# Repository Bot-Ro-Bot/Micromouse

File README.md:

# Micromouse
This project was done for participating in International Micromouse Competition organized by
[TechFest2019-20 at IIT Bombay](https://techfest.org/). It is
the furtherance of the Tremaux algorithm by employing a potential value algorithm in conjunction, with improving search in a micromouse.  The fused algorithm running on the STM32 Bluepill microcontroller explores and finds the shortest path in a 16x16 maze. Proximity sensors, gyroscope, and magnetometer together with encoder motors aid the micromouse to understand its surrounding hindrances and make precise movements while traversing through a maze. The optimized algorithm eliminates any paths that may lead the micromouse further away from the center of the maze during the initial run itself and saves a significant amount of time while solving a maze.

## Flow Chart of the Optimized Algorithm

Here are the three different versions of micromouse designed and fabricated. The bot at the center was used during the IMC-2020.

## Citation:
You can find our publication [here](https://ictaes.org/wp-content/uploads/2020/09/IJAE-2020-Vol.03-No.02/7_Sanjaya_Vol3_No2.pdf?ckattempt=1).
```
@article{rijalinternational,
  title={Optimizing Tremaux Algorithm in Micromouse Using Potential Values},
  journal={International Journal of Advanced Engineering},
  author={Rijal, Sanjay and Nepal, Rabin and Lwagun, Rhimesh and Pati, Rohit and Bhatta, Janardan},
  volume={3},
  issue={2},
  year={2020}
}

```

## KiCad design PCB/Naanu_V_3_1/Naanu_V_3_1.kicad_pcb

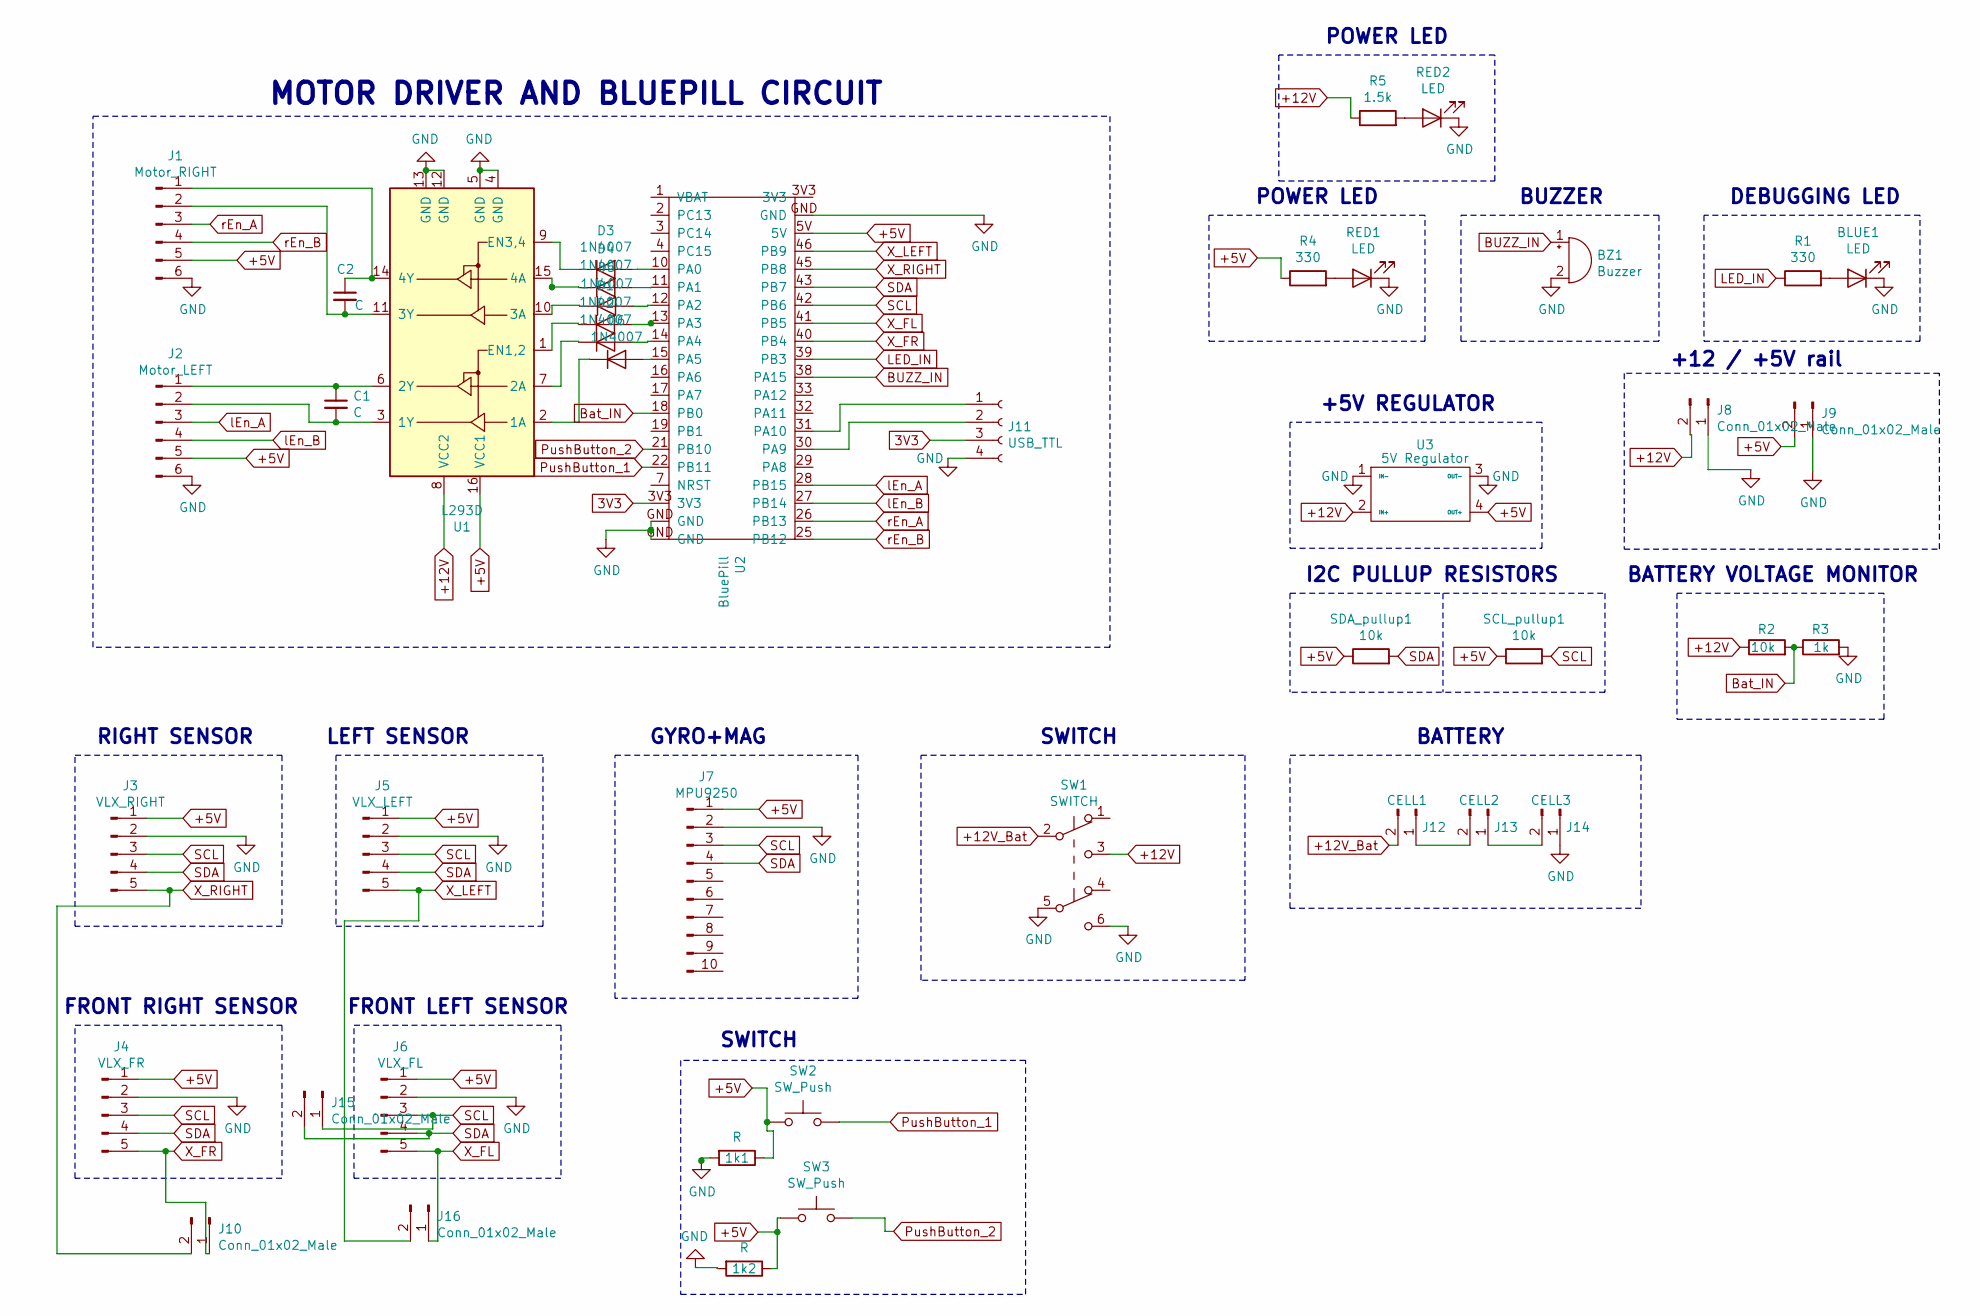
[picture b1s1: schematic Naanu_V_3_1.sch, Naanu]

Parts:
1k1, 1k2: R; R_Axial_DIN0207_L6.3mm_D2.5mm_P7.62mm_Horizontal
BLUE1: LED; LED_D3.0mm
BZ1: Buzzer; Buzzer_15x7.5RM7.6
C1, C2: C; C_Disc_D3.0mm_W1.6mm_P2.50mm
D1, D2, D3, D4, D5, D6: 1N4007; D_DO-41_SOD81_P7.62mm_Horizontal
J1: Motor_RIGHT; PinHeader_1x06_P2.54mm_Vertical
J2: Motor_LEFT; PinHeader_1x06_P2.54mm_Vertical
J3: VLX_RIGHT; PinHeader_1x05_P2.54mm_Horizontal
J4: VLX_FR; PinHeader_1x05_P2.54mm_Horizontal
J5: VLX_LEFT; PinHeader_1x05_P2.54mm_Horizontal
J6: VLX_FL; PinHeader_1x05_P2.54mm_Horizontal
J7: MPU9250; PinHeader_1x10_P2.54mm_Vertical
J8, J9, J10, J15, J16: Conn_01x02_Male; PinHeader_1x02_P2.54mm_Vertical
J11: USB_TTL; PinHeader_1x04_P2.54mm_Vertical
J12: CELL1; PinHeader_1x02_P2.54mm_Horizontal
J13: CELL2; PinHeader_1x02_P2.54mm_Horizontal
J14: CELL3; PinHeader_1x02_P2.54mm_Horizontal
R1, R4: 330; R_Axial_DIN0207_L6.3mm_D2.5mm_P7.62mm_Horizontal
R2: 10k; R_Axial_DIN0207_L6.3mm_D2.5mm_P7.62mm_Horizontal
R3: 1k; R_Axial_DIN0207_L6.3mm_D2.5mm_P7.62mm_Horizontal
R5: 1.5k; R_Axial_DIN0207_L6.3mm_D2.5mm_P7.62mm_Horizontal
RED1, RED2: LED; LED_D3.0mm
SCL_pullup1: 10k; R_Axial_DIN0207_L6.3mm_D2.5mm_P7.62mm_Horizontal
SDA_pullup1: 10k; R_Axial_DIN0207_L6.3mm_D2.5mm_P7.62mm_Horizontal
SW1: SWITCH; SW_CuK_JS202011CQN_DPDT_Straight
SW2, SW3: SW_Push; SW_PUSH_6mm_H5mm
U1: L293D; DIP-16_W7.62mm
U2: BluePill; STM32
U3: 5V Regulator; Buck

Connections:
3V3: J11.3, U2.3V3
+5V: 1k1.1, 1k2.1, J1.5, J2.5, J3.1, J4.1, J5.1, J6.1, J7.1, J9.2, R4.1, SCL_pullup1.1, SDA_pullup1.1, SW2.1, SW3.1, U1.16 (VCC1), U2.5V, U3.4 (OUT+)
+12V: J8.2, R2.1, R5.1, SW1.3 (C), U1.8 (VCC2), U3.2 (IN+)
+12V_Bat: J12.2, SW1.2 (B)
BUZZ_IN: BZ1.1 (-), U2.38 (PA15)
Bat_IN: R2.2, R3.1, U2.18 (PB0)
GND: 1k1.2, 1k2.2, BLUE1.1 (K), BZ1.2 (+), J1.6, J2.6, J3.2, J4.2, J5.2, J6.2, J7.2, J8.1, J9.1, J11.4, J14.1, R3.2, RED1.1 (K), RED2.1 (K), SW1.5 (B), SW1.6 (C), U1.4 (GND), U1.5 (GND), U1.12 (GND), U1.13 (GND), U2.GND, U3.1 (IN-), U3.3 (OUT-)
LED_IN: R1.1, U2.39 (PB3)
unnamed: BLUE1.2 (A), R1.2
unnamed: C1.1, J2.1, U1.6 (2Y)
unnamed: C1.2, J2.2, U1.3 (1Y)
unnamed: C2.1, J1.1, U1.14 (4Y)
unnamed: C2.2, J1.2, U1.11 (3Y)
unnamed: D1.1 (K), U1.1 (EN1,2)
unnamed: D1.2 (A), U2.13 (PA3)
unnamed: D2.1 (K), U1.7 (2A)
unnamed: D2.2 (A), U2.14 (PA4)
unnamed: D3.1 (K), U1.9 (EN3,4)
unnamed: D3.2 (A), U2.10 (PA0)
unnamed: D4.1 (K), U1.15 (4A)
unnamed: D4.2 (A), U2.11 (PA1)
unnamed: D5.1 (K), U1.10 (3A)
unnamed: D5.2 (A), U2.12 (PA2)
unnamed: D6.1 (K), U1.2 (1A)
unnamed: D6.2 (A), U2.15 (PA5)
unnamed: J11.1, U2.31 (PA10)
unnamed: J11.2, U2.30 (PA9)
unnamed: J12.1, J13.2
unnamed: J13.1, J14.2
unnamed: R4.2, RED1.2 (A)
unnamed: R5.2, RED2.2 (A)
PushButton_1: SW2.2, U2.22 (PB11)
PushButton_2: SW3.2, U2.21 (PB10)
SCL: J3.3, J4.3, J5.3, J6.3, J7.3, J15.1, SCL_pullup1.2, U2.42 (PB6)
SDA: J3.4, J4.4, J5.4, J6.4, J7.4, J15.2, SDA_pullup1.2, U2.43 (PB7)
X_FL: J6.5, J16.1, U2.41 (PB5)
X_FR: J4.5, J10.1, U2.40 (PB4)
X_LEFT: J5.5, J16.2, U2.46 (PB9)
X_RIGHT: J3.5, J10.2, U2.45 (PB8)
lEn_A: J2.3, U2.28 (PB15)
lEn_B: J2.4, U2.27 (PB14)
rEn_A: J1.3, U2.26 (PB13)
rEn_B: J1.4, U2.25 (PB12)

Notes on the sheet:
RIGHT SENSOR
LEFT SENSOR
FRONT RIGHT SENSOR
FRONT LEFT SENSOR
GYRO+MAG
SWITCH
I2C PULLUP RESISTORS
BUZZER
DEBUGGING LED
BATTERY VOLTAGE MONITOR
+5V REGULATOR
MOTOR DRIVER AND BLUEPILL CIRCUIT
POWER LED
BATTERY
+12 / +5V rail

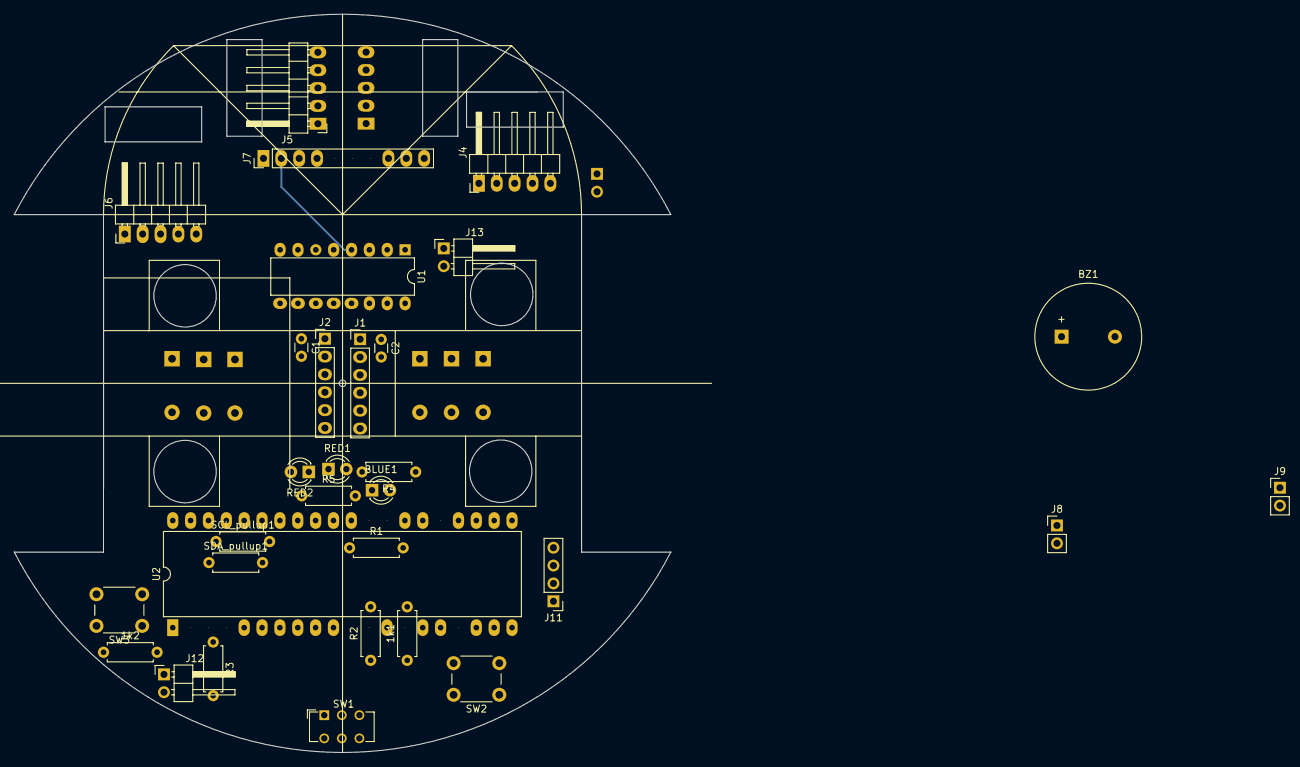
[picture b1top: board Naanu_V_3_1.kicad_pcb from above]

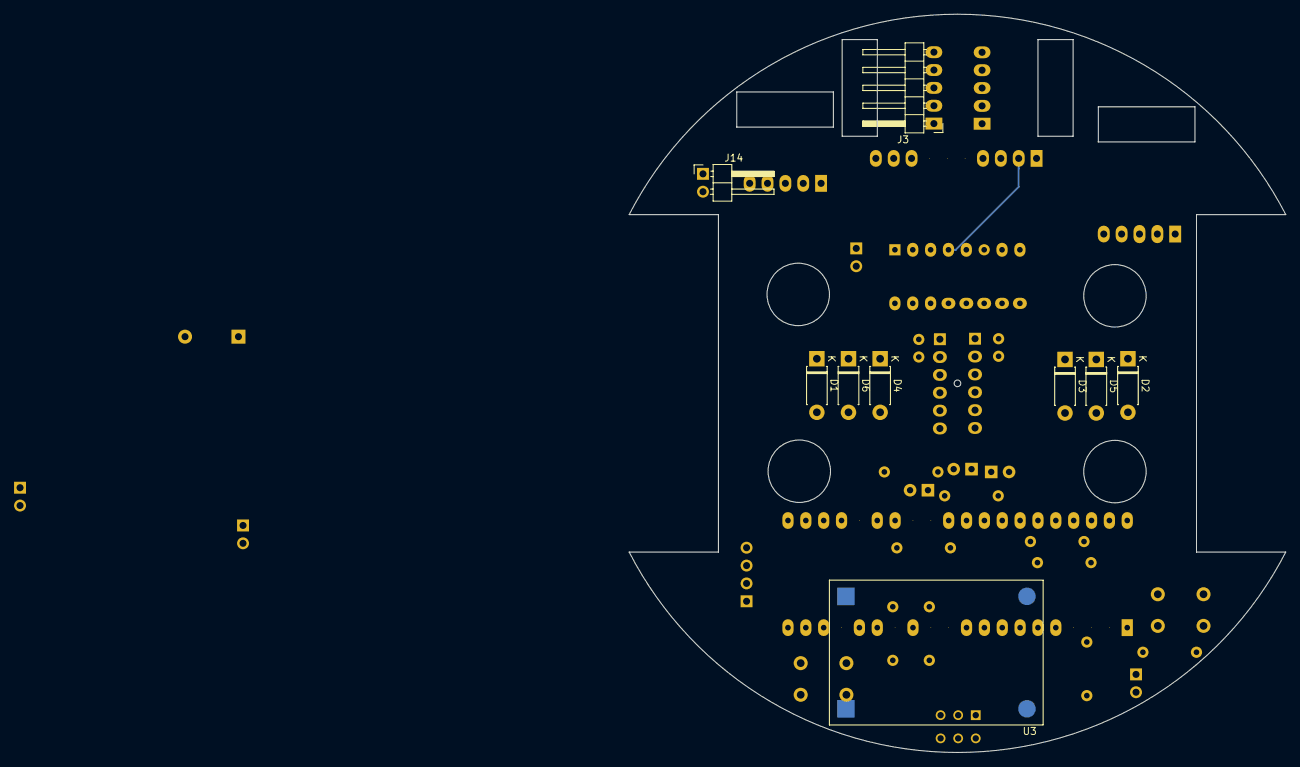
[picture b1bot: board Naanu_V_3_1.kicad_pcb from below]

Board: 2 copper layers, 93.4 x 105.0 mm, 40 parts (9 on the bottom side), 43 nets.

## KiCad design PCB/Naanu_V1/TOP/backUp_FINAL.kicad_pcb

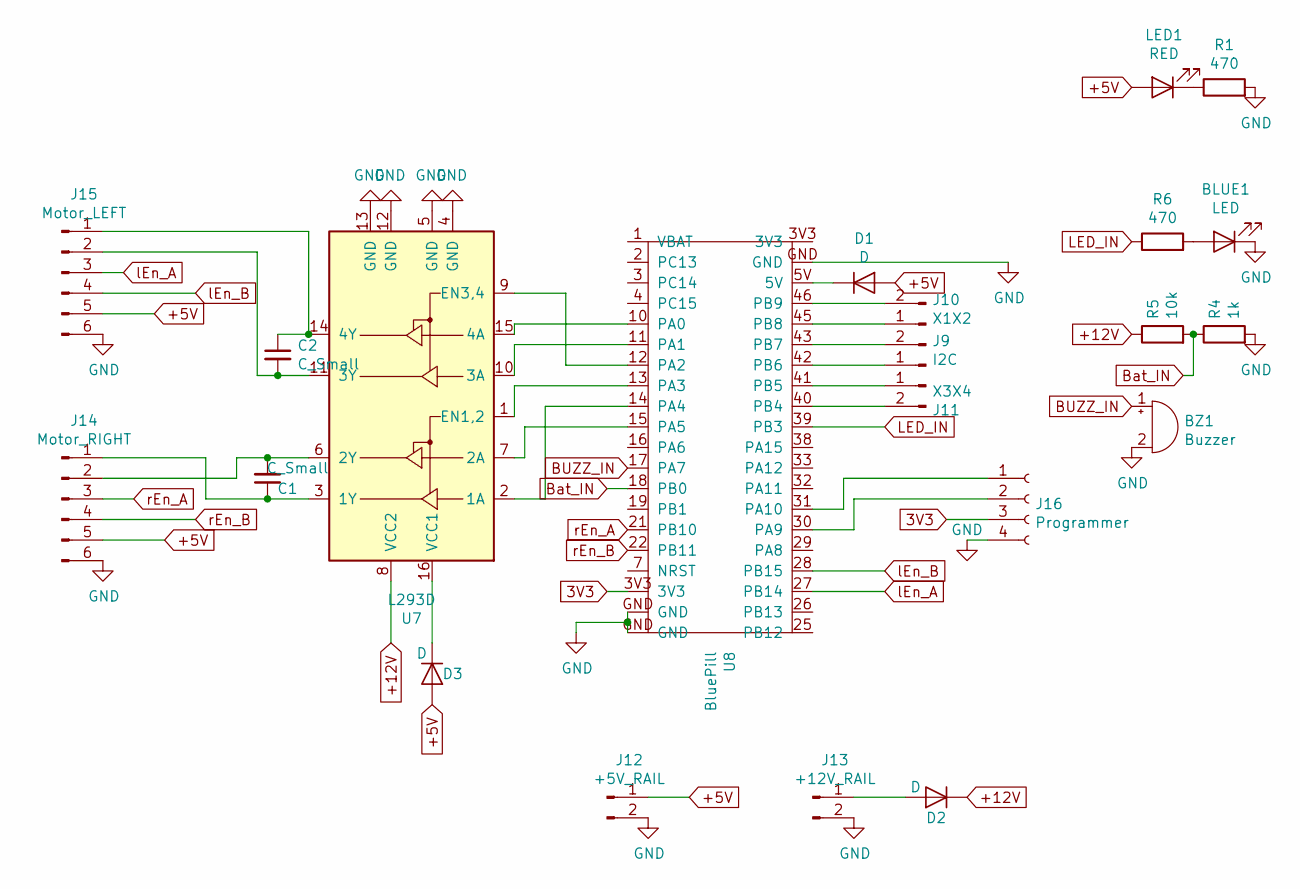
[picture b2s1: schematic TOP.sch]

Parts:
BLUE1: LED; LED_D3.0mm
BZ1: Buzzer; Buzzer_12x9.5RM7.6
C1, C2: C_Small; C_Disc_D3.0mm_W1.6mm_P2.50mm
D1, D2, D3: D; D_DO-41_SOD81_P7.62mm_Horizontal
J9: I2C; PinHeader_1x02_P2.54mm_Vertical
J10: X1X2; PinHeader_1x02_P2.54mm_Vertical
J11: X3X4; PinHeader_1x02_P2.54mm_Vertical
J12: +5V_RAIL; PinHeader_1x02_P2.54mm_Vertical
J13: +12V_RAIL; PinHeader_1x02_P2.54mm_Vertical
J14: Motor_RIGHT; PinHeader_1x06_P2.54mm_Vertical
J15: Motor_LEFT; PinHeader_1x06_P2.54mm_Vertical
J16: Programmer; PinHeader_1x04_P2.54mm_Vertical
LED1: RED; LED_D3.0mm
R1, R6: 470; R_Axial_DIN0207_L6.3mm_D2.5mm_P7.62mm_Horizontal
R4: 1k; R_Axial_DIN0207_L6.3mm_D2.5mm_P7.62mm_Horizontal
R5: 10k; R_Axial_DIN0207_L6.3mm_D2.5mm_P7.62mm_Horizontal
U7: L293D; DIP-16_W7.62mm_LongPads
U8: BluePill; STM32

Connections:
3V3: J16.3, U8.3V3
+5V: D1.2 (A), D3.2 (A), J12.1, J14.5, J15.5, LED1.2 (A)
+12V: D2.1 (K), R5.1, U7.8 (VCC2)
BUZZ_IN: BZ1.1 (-), U8.17 (PA7)
Bat_IN: R4.1, R5.2, U8.18 (PB0)
GND: BLUE1.1 (K), BZ1.2 (+), J12.2, J13.2, J14.6, J15.6, J16.4, R1.2, R4.2, U7.4 (GND), U7.5 (GND), U7.12 (GND), U7.13 (GND), U8.GND
LED_IN: R6.1, U8.39 (PB3)
unnamed: BLUE1.2 (A), R6.2
unnamed: C1.1, J14.1, U7.3 (1Y)
unnamed: C1.2, J14.2, U7.6 (2Y)
unnamed: C2.1, J15.1, U7.14 (4Y)
unnamed: C2.2, J15.2, U7.11 (3Y)
unnamed: D1.1 (K), U8.5V
unnamed: D2.2 (A), J13.1
unnamed: D3.1 (K), U7.16 (VCC1)
unnamed: J9.1, U8.42 (PB6)
unnamed: J9.2, U8.43 (PB7)
unnamed: J10.1, U8.45 (PB8)
unnamed: J10.2, U8.46 (PB9)
unnamed: J11.1, U8.41 (PB5)
unnamed: J11.2, U8.40 (PB4)
unnamed: J16.1, U8.31 (PA10)
unnamed: J16.2, U8.30 (PA9)
unnamed: LED1.1 (K), R1.1
unnamed: U7.1 (EN1,2), U8.13 (PA3)
unnamed: U7.2 (1A), U8.14 (PA4)
unnamed: U7.7 (2A), U8.15 (PA5)
unnamed: U7.9 (EN3,4), U8.12 (PA2)
unnamed: U7.10 (3A), U8.11 (PA1)
unnamed: U7.15 (4A), U8.10 (PA0)
lEn_A: J15.3, U8.27 (PB14)
lEn_B: J15.4, U8.28 (PB15)
rEn_A: J14.3, U8.21 (PB10)
rEn_B: J14.4, U8.22 (PB11)

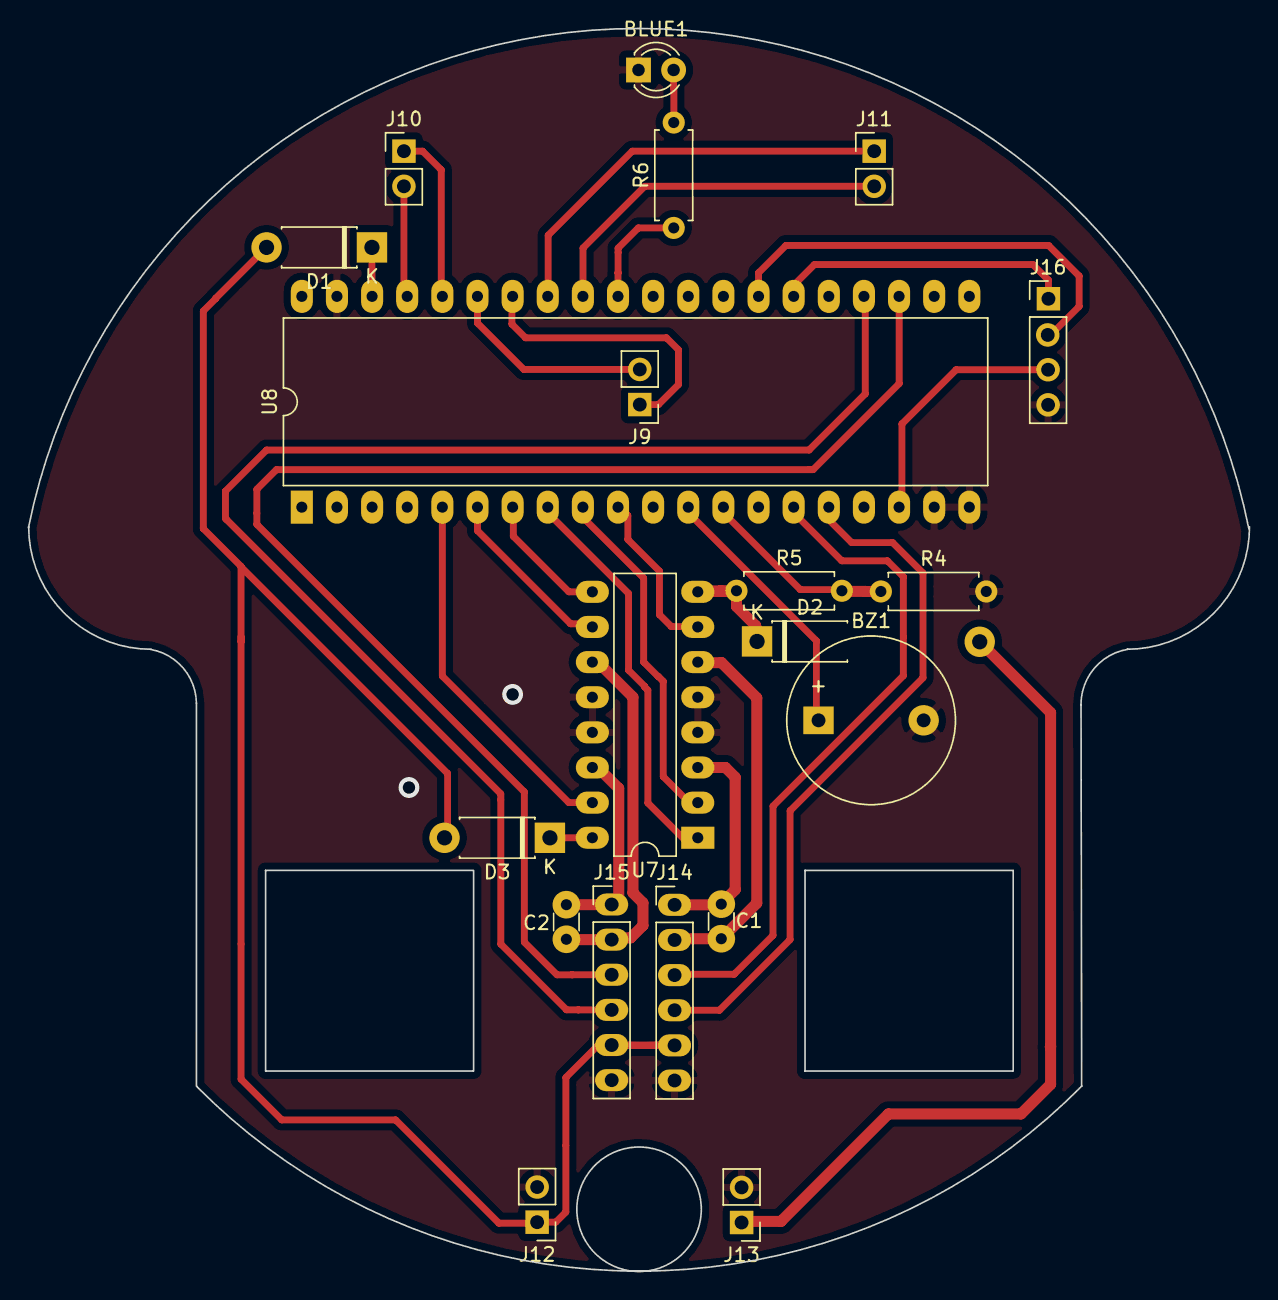
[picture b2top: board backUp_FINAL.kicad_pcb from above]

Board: 2 copper layers, 88.3 x 89.8 mm, 20 parts (0 on the bottom side), 33 nets.

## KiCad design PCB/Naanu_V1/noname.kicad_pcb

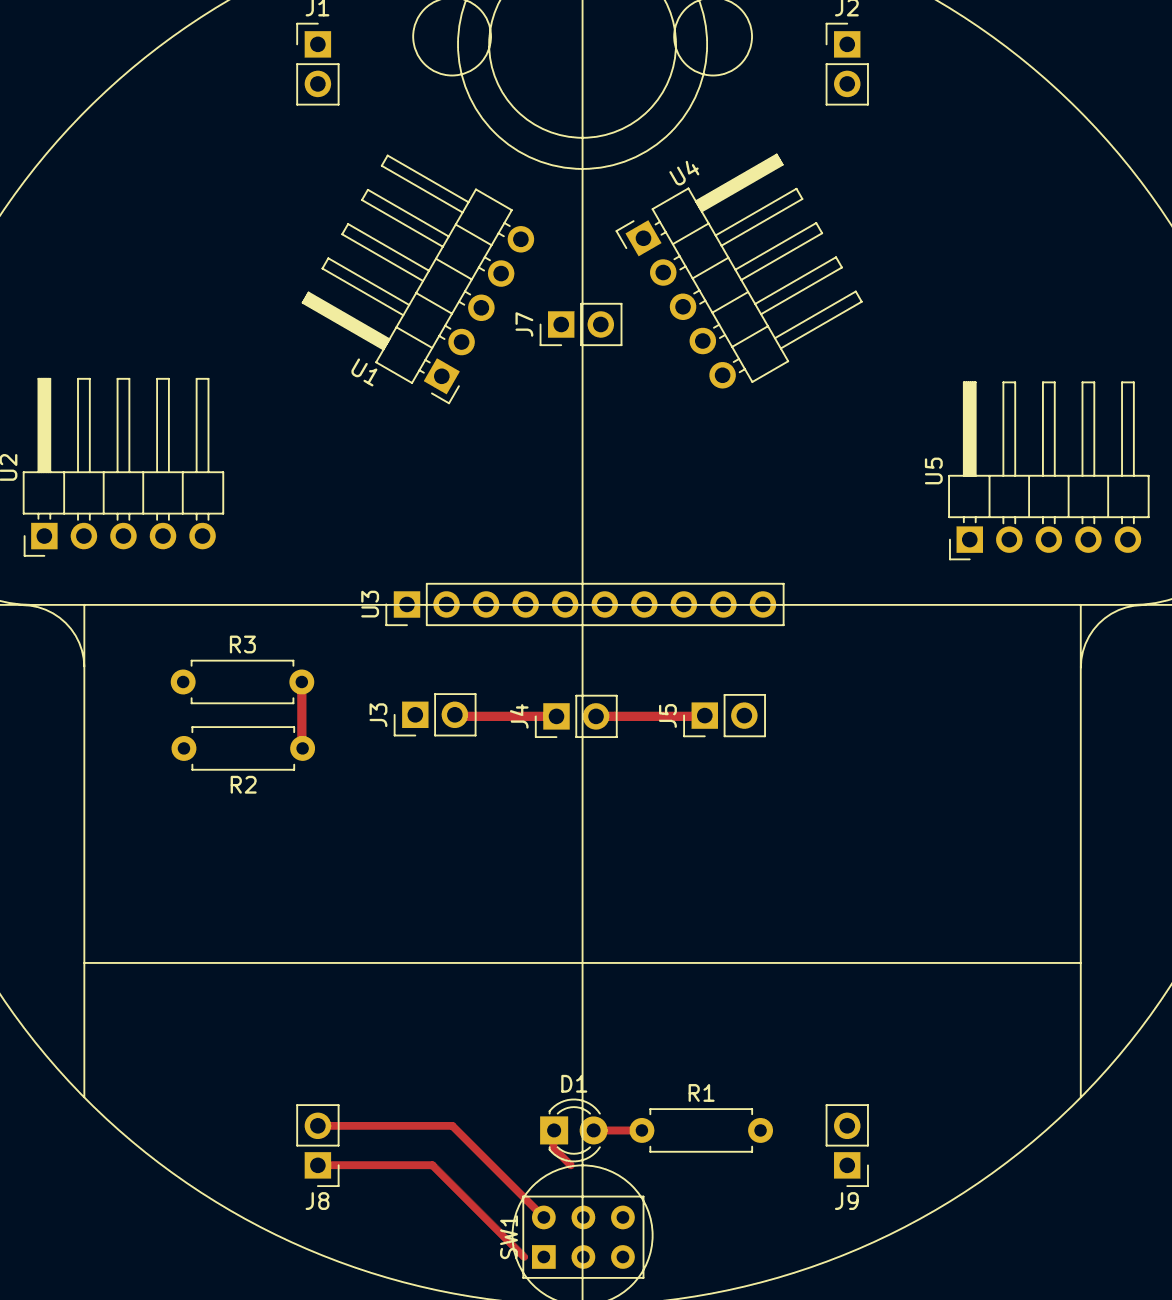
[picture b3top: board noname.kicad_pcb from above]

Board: 2 copper layers, 18 parts (0 on the bottom side), 15 nets.

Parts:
D1: BLUE; LED_D3.0mm
J1: X1X2; PinHeader_1x02_P2.54mm_Vertical
J2: X3X4; PinHeader_1x02_P2.54mm_Vertical
J3: CELL_3; PinHeader_1x02_P2.54mm_Vertical
J4: CELL_2; PinHeader_1x02_P2.54mm_Vertical
J5: CELL_1; PinHeader_1x02_P2.54mm_Vertical
J7: I2C; PinHeader_1x02_P2.54mm_Vertical
J8: 12V_RAIL; PinHeader_1x02_P2.54mm_Vertical
J9: +5V_RAIL; PinHeader_1x02_P2.54mm_Vertical
R1: 470; R_Axial_DIN0207_L6.3mm_D2.5mm_P7.62mm_Horizontal
R2, R3: 10k; R_Axial_DIN0207_L6.3mm_D2.5mm_P7.62mm_Horizontal
SW1: SW_Push_DPDT; SW_NKK_G1xJP
U1, U2, U4, U5: Vl530lx; PinHeader_1x05_P2.54mm_Horizontal
U3: MPU9250; PinHeader_1x10_P2.54mm_Vertical

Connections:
unnamed: D1.1, J9.2, U1.4, U2.4, U3.2, U4.4, U5.4
unnamed: D1.2, R1.1
unnamed: J1.1, U1.1
unnamed: J1.2, U2.1
unnamed: J2.1, U5.1
unnamed: J2.2, U4.1
unnamed: J3.1, SW1.2
unnamed: J3.2, J4.1
unnamed: J4.2, J5.1
unnamed: J5.2, SW1.5
unnamed: J7.1, R2.2, U1.3, U2.3, U3.3, U4.3, U5.3
unnamed: J7.2, R3.1, U1.2, U2.2, U3.4, U4.2, U5.2
unnamed: J8.1, SW1.3
unnamed: J8.2, SW1.6
unnamed: J9.1, R1.2, R2.1, R3.2, U1.5, U2.5, U3.1, U4.5, U5.5

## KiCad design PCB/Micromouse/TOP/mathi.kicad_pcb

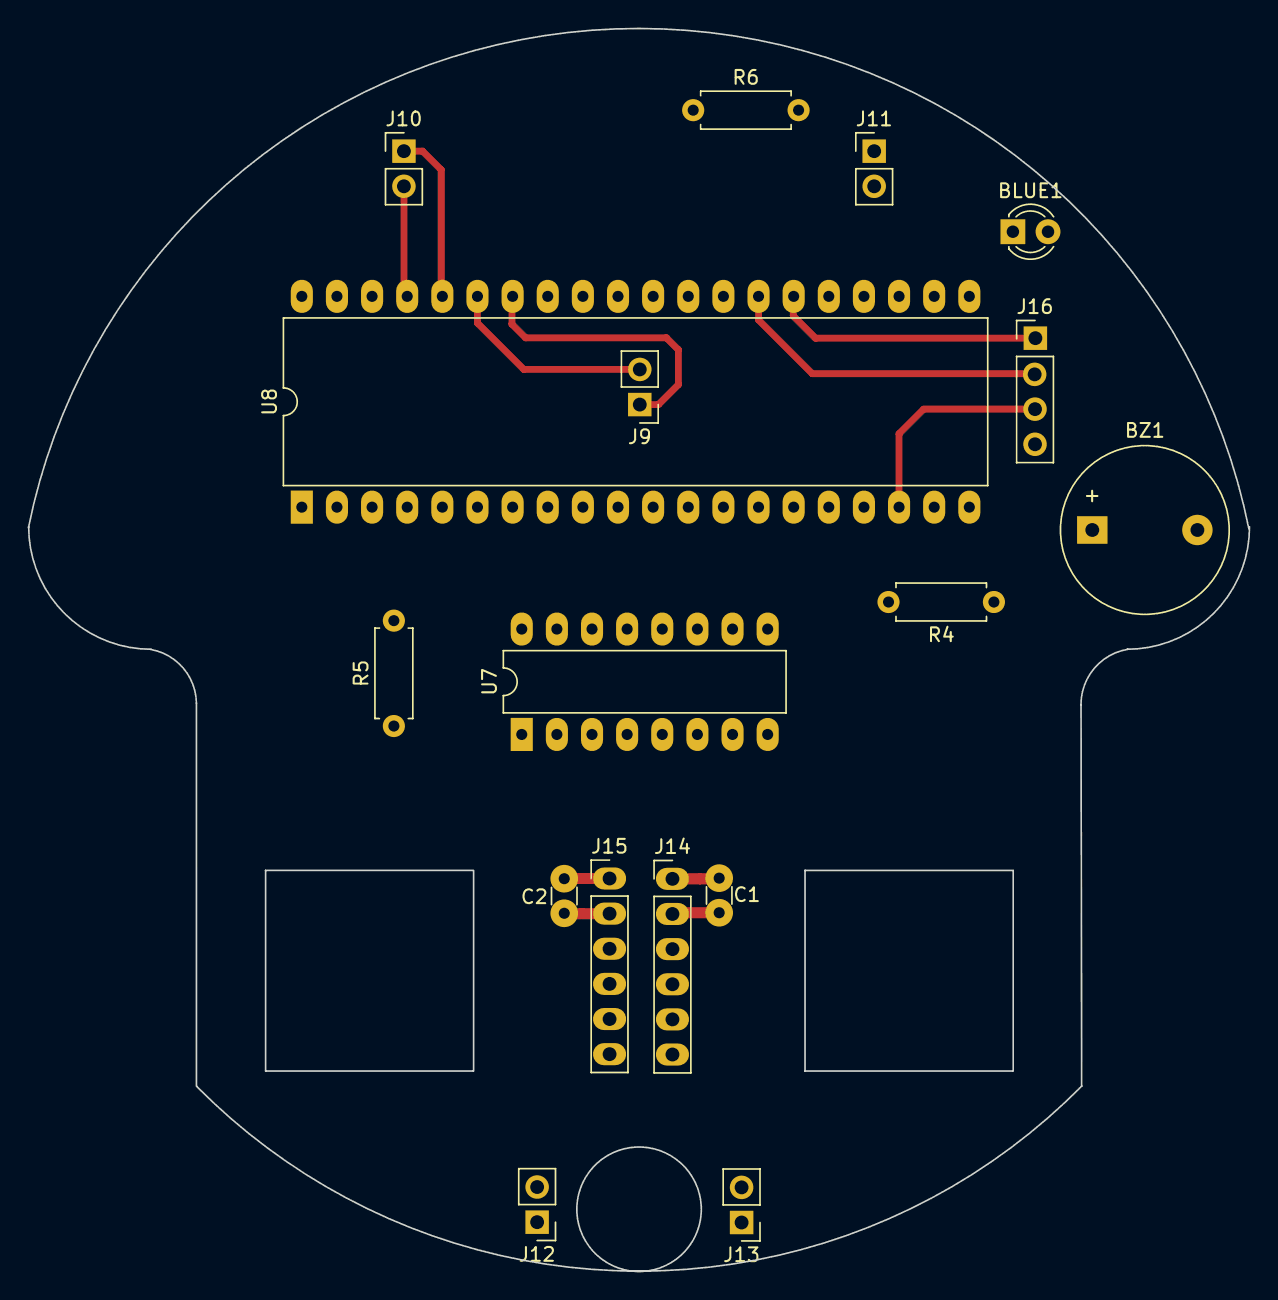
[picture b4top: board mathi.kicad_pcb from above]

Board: 2 copper layers, 88.3 x 89.8 mm, 17 parts (0 on the bottom side), 30 nets.

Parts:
BLUE1: LED; LED_D3.0mm
BZ1: Buzzer; Buzzer_12x9.5RM7.6
C1, C2: C_Small; C_Disc_D3.0mm_W1.6mm_P2.50mm
J9: I2C; PinHeader_1x02_P2.54mm_Vertical
J10: X1X2; PinHeader_1x02_P2.54mm_Vertical
J11: X3X4; PinHeader_1x02_P2.54mm_Vertical
J12: +5V_RAIL; PinHeader_1x02_P2.54mm_Vertical
J13: +12V_RAIL; PinHeader_1x02_P2.54mm_Vertical
J14: Motor_RIGHT; PinHeader_1x06_P2.54mm_Vertical
J15: Motor_LEFT; PinHeader_1x06_P2.54mm_Vertical
J16: Programmer; PinHeader_1x04_P2.54mm_Vertical
R4: 1k; R_Axial_DIN0207_L6.3mm_D2.5mm_P7.62mm_Horizontal
R5: 10k; R_Axial_DIN0207_L6.3mm_D2.5mm_P7.62mm_Horizontal
R6: 470; R_Axial_DIN0207_L6.3mm_D2.5mm_P7.62mm_Horizontal
U7: L293D; DIP-16_W7.62mm_LongPads
U8: BluePill; STM32

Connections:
3V3: J16.3, U8.3V3
+5V: J12.1, J14.5, J15.5, U7.16, U8.5V
+12V: J13.1, R5.1, U7.8
BUZZ_IN: BZ1.1, U8.38
Bat_IN: R4.1, R5.2, U8.18
GND: BLUE1.1, BZ1.2, J12.2, J13.2, J14.6, J15.6, J16.4, R4.2, U7.4, U7.5, U7.12, U7.13, U8.GND
LED_IN: R6.1, U8.39
unnamed: BLUE1.2, R6.2
unnamed: C1.1, J14.1, U7.14
unnamed: C1.2, J14.2, U7.11
unnamed: C2.1, J15.1, U7.6
unnamed: C2.2, J15.2, U7.3
unnamed: J9.1, U8.42
unnamed: J9.2, U8.43
unnamed: J10.1, U8.45
unnamed: J10.2, U8.46
unnamed: J11.1, U8.40
unnamed: J11.2, U8.41
unnamed: J16.1, U8.31
unnamed: J16.2, U8.30
unnamed: U7.1, U8.13
unnamed: U7.2, U8.15
unnamed: U7.7, U8.14
unnamed: U7.9, U8.10
unnamed: U7.10, U8.12
unnamed: U7.15, U8.11
lEn_A: J15.3, U8.28
lEn_B: J15.4, U8.27
rEn_A: J14.3, U8.26
rEn_B: J14.4, U8.25

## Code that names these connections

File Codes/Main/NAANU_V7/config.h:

#pragma once
///////////////////////////////////////////////////////////*********VLX_DEFINITIONS**********/////////////////////////////////////////////////////////////////////
//////////////////////////////////////////////////////////////////////////////////////////////////////////////////////////////////////////////////////////////////
#define frontRightAddress 0x30
#define frontLeftAddress 0x31
#define rightAddress 0x32
#define leftAddress 0x33

#define xshutLeft PB8
#define xshutRight PB5
#define xshutFrontRight PB4
#define xshutFrontLeft PB9
//////////////////////////////////////////////////////////////////////////////////////////////////////////////////////////////////////////////////////////////////
//////////////////////////////////////////////////////////////////////////////////////////////////////////////////////////////////////////////////////////////////



///////////////////////////////////////////////////////////*********MPU_DEFINITIONS**********//////////////////////////////////////////////////////////////////////
///////////////////////////////////////////////////////////////////////////////////////////////////////////////////////////////////////////////////////////////////
#define MPU_Address 0x68
#define Mag_Address 0x0C
///////////////////////////////////////////////////////////////////////////////////////////////////////////////////////////////////////////////////////////////////
///////////////////////////////////////////////////////////////////////////////////////////////////////////////////////////////////////////////////////////////////



///////////////////////////////////////////////////////////*********MOTOR_DEFINITIONS**********////////////////////////////////////////////////////////////////////
///////////////////////////////////////////////////////////////////////////////////////////////////////////////////////////////////////////////////////////////////
#define lMotorEnable PA2
#define lMotorForward PA1
#define lMotorBack PA0

#define rMotorEnable PA3
#define rMotorForward PA4
#define rMotorBack PA5

#define rEncoderA PB10
#define rEncoderB PB11
#define lEncoderA PB15
#define lEncoderB PB14

#define baseSpeed 32
///////////////////////////////////////////////////////////////////////////////////////////////////////////////////////////////////////////////////////////////////
///////////////////////////////////////////////////////////////////////////////////////////////////////////////////////////////////////////////////////////////////



///////////////////////////////////////////////////////////*********BATTERY_DEFINITIONS**********//////////////////////////////////////////////////////////////////
///////////////////////////////////////////////////////////////////////////////////////////////////////////////////////////////////////////////////////////////////
#define BATTERY_PIN PB0
///////////////////////////////////////////////////////////////////////////////////////////////////////////////////////////////////////////////////////////////////
///////////////////////////////////////////////////////////////////////////////////////////////////////////////////////////////////////////////////////////////////



///////////////////////////////////////////////////////////*********DEBUGGING_DEFINITIONS**********//////////////////////////////////////////////////////////////////
///////////////////////////////////////////////////////////////////////////////////////////////////////////////////////////////////////////////////////////////////
#define BUZZER_PIN PA7
#define LED_PIN PB3

#define BUZZER_ON   (GPIOA_BASE->BSRR |= (1 << 7 ))
#define BUZZER_OFF  (GPIOA_BASE->BSRR |= (1 << 23))

#define BLUE_HIGH   (GPIOB_BASE->BSRR |= (1 << 3))
#define BLUE_LOW    (GPIOB_BASE->BSRR |= (1 << 19))
#define led PB4

///////////////////////////////////////////////////////////////////////////////////////////////////////////////////////////////////////////////////////////////////
///////////////////////////////////////////////////////////////////////////////////////////////////////////////////////////////////////////////////////////////////



///////////////////////////////////////////////////////////*********EEPROM_DEFINITIONS**********///////////////////////////////////////////////////////////////////
///////////////////////////////////////////////////////////////////////////////////////////////////////////////////////////////////////////////////////////////////
#define Page0 0x0801F000
#define Page1 0x0801F400
#define Page2 0x0801F800
#define Page3 0x0801FC00
#define PageSize 0x400  //1 kb size
#define baseAddress 0x0801F000
#define flagAddress 0x0801F402
///////////////////////////////////////////////////////////////////////////////////////////////////////////////////////////////////////////////////////////////////
///////////////////////////////////////////////////////////////////////////////////////////////////////////////////////////////////////////////////////////////////

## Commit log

2020-05-01 Added Schematics of Naanu_V3
2020-05-07 Added List of Important Sites
2020-05-07 Added simulator site
2020-05-10 Deleting for rearrangement
2020-05-10 Managed Files
2020-05-10 deleted files and added schematic
2020-05-10 added codes folder
2020-05-11 Added lower versions
2020-05-12 Added MPU9050 research document
2021-05-28 Updates merged to main (#4)
    * Deleting for rearrangement
    * Delete viber image 2019-10-26 , 10.37.09.jpg
    * Deleting for rearrangement
    * Deleting for rearrangement
    * Deleting for rearrangement
    * Delete Naanu Schematic.pdf
2022-04-13 Hardware References
2022-04-13 Algorithm references
2022-04-13 misc refs
2022-04-13 implementation and documentation figures
2023-01-25 added cite
2023-02-27 deleted duplicate flow chart image
2023-02-27 minor changes
2023-02-27 updated bib field
2023-05-01 updated documentation-related stuffs (#5)
    * Hardware References
    * Algorithm references
    * misc refs
    * implementation and documentation figures
    * Add files via upload
    * Update README.md
2023-08-04 added link, fixed typos
